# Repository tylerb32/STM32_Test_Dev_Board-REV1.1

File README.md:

# STM32_Test_Dev_Board-REV1.1
*Currently a work in progress<br/>
The purpose of this project is to gain experience with embedded system design, electronics and PCB design, and firmware/real-time software development in FreeRTOS.<br/>
Status: PCBs assembled (Investigating accelerometer hardware implementation).

Changes from REV 1:
- Changed component selection for MCU, crystal oscillator, and accelerometer due to availability and cost constraints
- Added switches for user input
- Improved positioning of LCD headers and ensured the screen won't block any other headers or connectors when plugged in
- Changed micro USB footprint
- Routed CBUS pins from UART-USB bridge and interrupt pins from the accelerometer to the MCU instead of external headers
- Routed remaining pins including LPUART to external headers

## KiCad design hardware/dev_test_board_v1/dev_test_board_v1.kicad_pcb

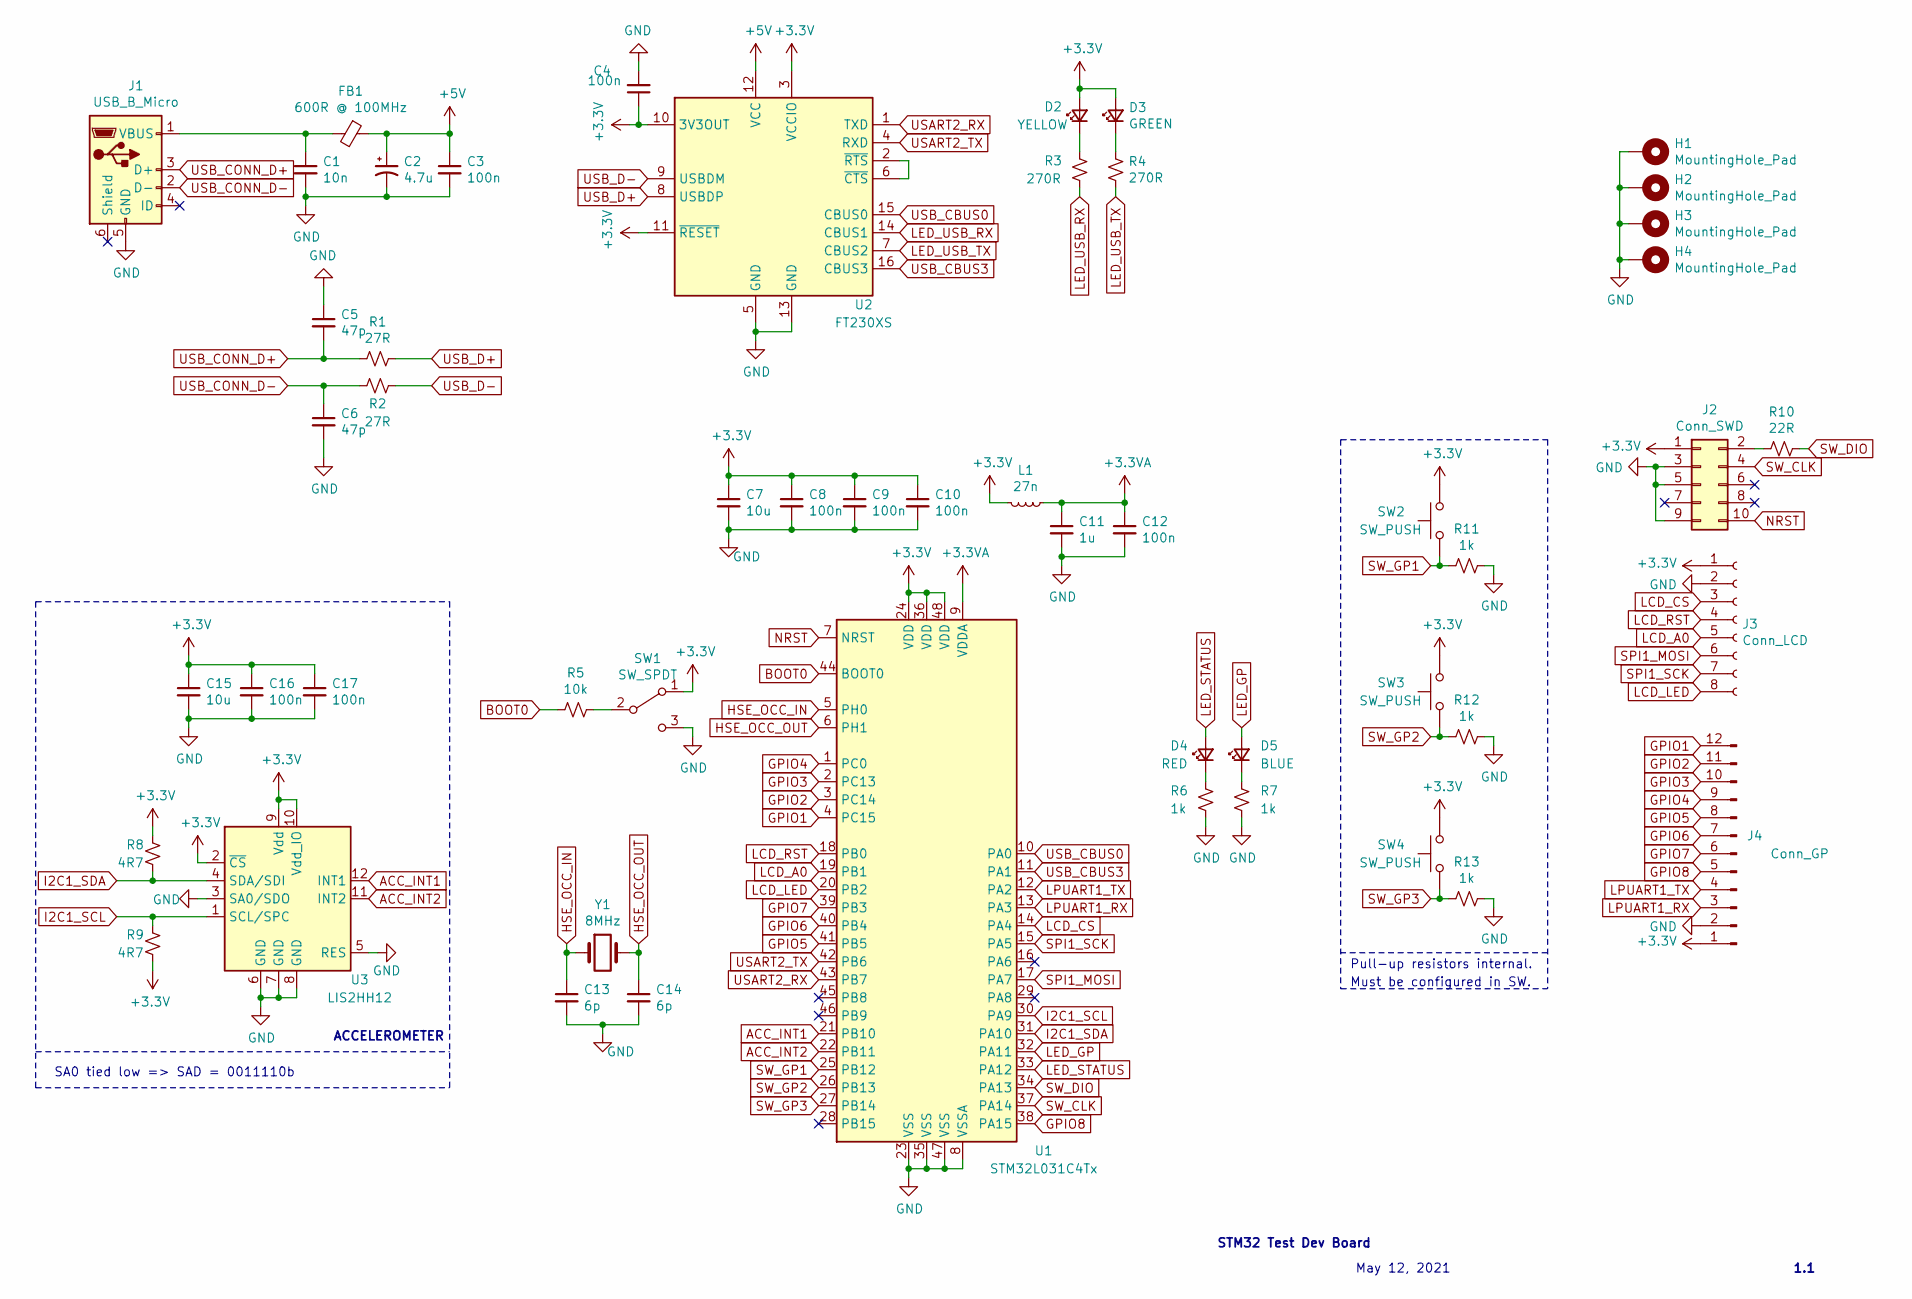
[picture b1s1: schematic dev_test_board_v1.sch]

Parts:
C1: 10n; C_0603_1608Metric
C2: 4.7u; CP_Elec_4x5.4
C3, C4, C8, C9, C10, C12, C16, C17: 100n; C_0402_1005Metric
C5, C6: 47p; C_0603_1608Metric
C7, C15: 10u; C_0402_1005Metric
C11: 1u; C_0402_1005Metric
C13, C14: 6p; C_0402_1005Metric
D2: YELLOW; LED_0603_1608Metric
D3: GREEN; LED_0603_1608Metric
D4: RED; LED_0603_1608Metric
D5: BLUE; LED_0603_1608Metric
FB1: 600R @ 100MHz; L_0805_2012Metric
H1, H2, H3, H4: MountingHole_Pad; MountingHole_2.7mm_M2.5_Pad_Via
J1: USB_B_Micro; UBS_Micro-B_Citzends_Aliexpress
J2: Conn_SWD; PinHeader_2x05_P1.27mm_Vertical
J3: Conn_LCD; PinSocket_1x08_P2.54mm_Vertical
J4: Conn_GP; PinHeader_1x12_P2.54mm_Vertical
L1: 27n; L_0603_1608Metric
R1, R2: 27R; R_0402_1005Metric
R3, R4: 270R; R_0603_1608Metric
R5: 10k; R_0402_1005Metric
R6, R7: 1k; R_0603_1608Metric
R8, R9: 4R7; R_0402_1005Metric
R10: 22R; R_0402_1005Metric
R11, R12, R13: 1k; R_0402_1005Metric
SW1: SW_SPDT; SW_Unknown_SPDT_Straight
SW2, SW3, SW4: SW_PUSH; SW_Push_1P1T_NO_6x6mm_H9.5mm
U1: STM32L031C4Tx; LQFP-48_7x7mm_P0.5mm
U2: FT230XS; SSOP-16_3.9x4.9mm_P0.635mm
U3: LIS2HH12; LGA-12_2x2mm_P0.5mm
Y1: 8MHz; Crystal_NX8045GB

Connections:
+3.3VA: C11.1, C12.1, L1.1, U1.9 (VDDA)
+3V3: C4.1, C7.1, C8.1, C9.1, C10.1, C15.1, C16.1, C17.1, D2.2 (A), D3.2 (A), J2.1, J3.1, J4.1, L1.2, R8.2, R9.1, SW1.1 (A), SW2.2, SW3.2, SW4.2, U1.24 (VDD), U1.36 (VDD), U1.48 (VDD), U2.3 (VCCIO), U2.10 (3V3OUT), U2.11 (~RESET), U3.2 (~CS), U3.9 (Vdd), U3.10 (Vdd_IO)
+5V: C2.1, C3.1, FB1.1, U2.12 (VCC)
ACC_INT1: U1.21 (PB10), U3.12 (INT1)
ACC_INT2: U1.22 (PB11), U3.11 (INT2)
BOOT0: R5.2, U1.44 (BOOT0)
GND: C1.2, C2.2, C3.2, C4.2, C5.1, C6.2, C7.2, C8.2, C9.2, C10.2, C11.2, C12.2, C13.2, C14.2, C15.2, C16.2, C17.2, H1.1, H2.1, H3.1, H4.1, J1.5 (GND), J2.3, J2.5, J2.9, J3.2, J4.2, R6.2, R7.2, R11.1, R12.1, R13.1, SW1.3 (C), U1.8 (VSSA), U1.23 (VSS), U1.35 (VSS), U1.47 (VSS), U2.5 (GND), U2.13 (GND), U3.3 (SA0/SDO), U3.5 (RES), U3.6 (GND), U3.7 (GND), U3.8 (GND)
GPIO1: J4.12, U1.4 (PC15)
GPIO2: J4.11, U1.3 (PC14)
GPIO3: J4.10, U1.2 (PC13)
GPIO4: J4.9, U1.1 (PC0)
GPIO5: J4.8, U1.41 (PB5)
GPIO6: J4.7, U1.40 (PB4)
GPIO7: J4.6, U1.39 (PB3)
GPIO8: J4.5, U1.38 (PA15)
HSE_OCC_IN: C13.1, U1.5 (PH0), Y1.1
HSE_OCC_OUT: C14.1, U1.6 (PH1), Y1.2
I2C1_SCL: R9.2, U1.30 (PA9), U3.1 (SCL/SPC)
I2C1_SDA: R8.1, U1.31 (PA10), U3.4 (SDA/SDI)
LCD_A0: J3.5, U1.19 (PB1)
LCD_CS: J3.3, U1.14 (PA4)
LCD_LED: J3.8, U1.20 (PB2)
LCD_RST: J3.4, U1.18 (PB0)
LED_GP: D5.2 (A), U1.32 (PA11)
LED_STATUS: D4.2 (A), U1.33 (PA12)
LED_USB_RX: R3.2, U2.14 (CBUS1)
LED_USB_TX: R4.2, U2.7 (CBUS2)
LPUART1_RX: J4.3, U1.13 (PA3)
LPUART1_TX: J4.4, U1.12 (PA2)
NRST: J2.10, U1.7 (NRST)
unnamed: C1.1, FB1.2, J1.1 (VBUS)
unnamed: D2.1 (K), R3.1
unnamed: D3.1 (K), R4.1
unnamed: D4.1 (K), R6.1
unnamed: D5.1 (K), R7.1
unnamed: J2.2, R10.2
unnamed: R5.1, SW1.2 (B)
unnamed: U2.2 (~RTS), U2.6 (~CTS)
SPI1_MOSI: J3.6, U1.17 (PA7)
SPI1_SCK: J3.7, U1.15 (PA5)
SW_CLK: J2.4, U1.37 (PA14)
SW_DIO: R10.1, U1.34 (PA13)
SW_GP1: R11.2, SW2.1, U1.25 (PB12)
SW_GP2: R12.2, SW3.1, U1.26 (PB13)
SW_GP3: R13.2, SW4.1, U1.27 (PB14)
USART2_RX: U1.43 (PB7), U2.1 (TXD)
USART2_TX: U1.42 (PB6), U2.4 (RXD)
USB_CBUS0: U1.10 (PA0), U2.15 (CBUS0)
USB_CBUS3: U1.11 (PA1), U2.16 (CBUS3)
USB_CONN_D+: C5.2, J1.3 (D+), R1.2
USB_CONN_D-: C6.1, J1.2 (D-), R2.2
USB_D+: R1.1, U2.8 (USBDP)
USB_D-: R2.1, U2.9 (USBDM)

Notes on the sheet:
May 12, 2021
STM32 Test Dev Board
1.1
SA0 tied low => SAD = 0011110b
ACCELEROMETER
Pull-up resistors internal.
Must be configured in SW.

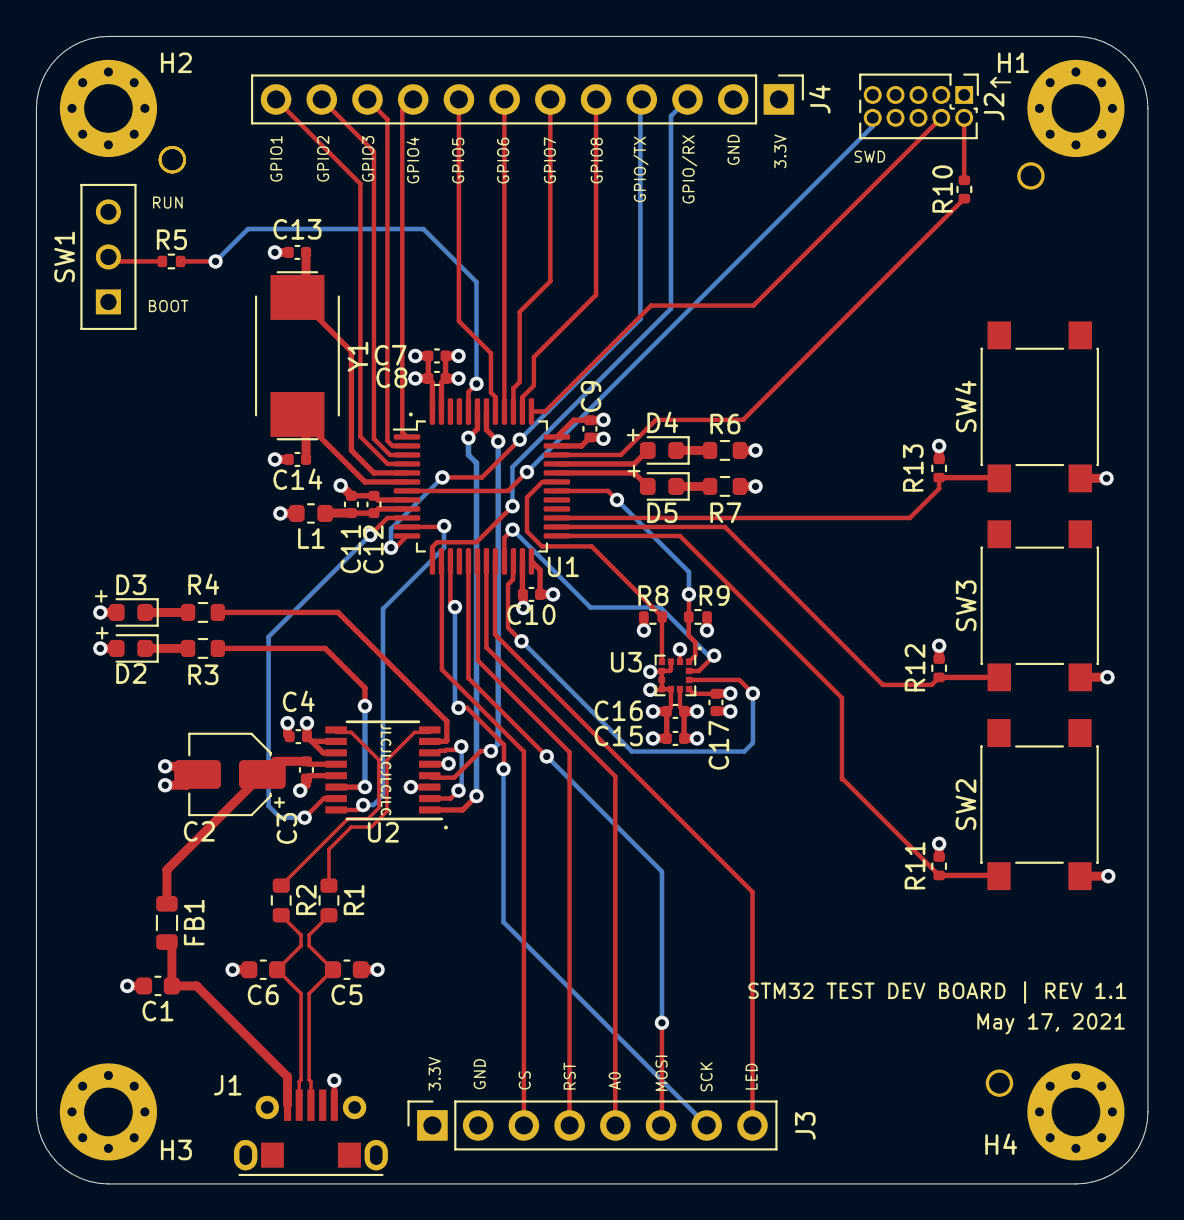
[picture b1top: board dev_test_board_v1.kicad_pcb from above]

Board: 4 copper layers, 61.8 x 63.8 mm, 52 parts (0 on the bottom side), 53 nets.

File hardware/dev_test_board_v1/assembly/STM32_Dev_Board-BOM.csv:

Comment,Designator,Footprint,LCSC
10n,C1,Capacitor_SMD:C_0603_1608Metric,C57112
1u,C11,Capacitor_SMD:C_0402_1005Metric,C52923
6p,"C13,C14",Capacitor_SMD:C_0402_1005Metric,C30274
10u,"C7,C15",Capacitor_SMD:C_0402_1005Metric,C15525
4.7u,C2,Capacitor_SMD:CP_Elec_4x5.4,
100n,"C3,C4,C8,C9,C10,C12,C16,C17",Capacitor_SMD:C_0402_1005Metric,C1525
47p,"C5,C6",Capacitor_SMD:C_0603_1608Metric,C1671
YELLOW,D2,LED_SMD:LED_0603_1608Metric,C72038
GREEN,D3,LED_SMD:LED_0603_1608Metric,C72043
RED,D4,LED_SMD:LED_0603_1608Metric,C2286
BLUE,D5,LED_SMD:LED_0603_1608Metric,C72041
600R @ 100MHz,FB1,Inductor_SMD:L_0805_2012Metric,C1017
MountingHole_Pad,"H1,H2,H3,H4",MountingHole:MountingHole_2.7mm_M2.5_Pad_Via,
USB_B_Micro,J1,tyjba_footprints:UBS_Micro-B_Citzends_Aliexpress,
Conn_SWD,J2,Connector_PinHeader_1.27mm:PinHeader_2x05_P1.27mm_Vertical,
Conn_LCD,J3,Connector_PinSocket_2.54mm:PinSocket_1x08_P2.54mm_Vertical,
Conn_GP,J4,Connector_PinHeader_2.54mm:PinHeader_1x12_P2.54mm_Vertical,
27n,L1,Inductor_SMD:L_0603_1608Metric,C12100
22R,R10,Resistor_SMD:R_0402_1005Metric,C25092
1k,"R11,R12,R13",Resistor_SMD:R_0402_1005Metric,C11702
27R,"R1,R2",Resistor_SMD:R_0603_1608Metric,C25190
270R,"R3,R4",Resistor_SMD:R_0603_1608Metric,C22966
10k,R5,Resistor_SMD:R_0402_1005Metric,C25744
1k,"R6,R7",Resistor_SMD:R_0603_1608Metric,C21190
4R7,"R8,R9",Resistor_SMD:R_0402_1005Metric,C25900
SW_SPDT,SW1,tyjba_footprints:SW_Unknown_SPDT_Straight,
SW_PUSH,"SW2,SW3,SW4",Button_Switch_SMD:SW_Push_1P1T_NO_6x6mm_H9.5mm,
STM32L031C4Tx,U1,Package_QFP:LQFP-48_7x7mm_P0.5mm,
FT230XS,U2,Package_SO:SSOP-16_3.9x4.9mm_P0.635mm,
LIS2HH12,U3,Package_LGA:LGA-12_2x2mm_P0.5mm,
8MHz,Y1,tyjba_footprints:Crystal_NX8045GB,

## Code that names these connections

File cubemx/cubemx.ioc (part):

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Mcu.Name=STM32L031C(4-6)Tx
Mcu.Package=LQFP48
Mcu.UserName=STM32L031C4Tx
PA0.Signal=GPIO_Output
PA1.Signal=GPIO_Output
PA10.Mode=I2C
PA10.Signal=I2C1_SDA
PA11.Signal=GPIO_Output
PA12.Signal=GPIO_Output
PA13.Mode=Serial_Wire
PA13.Signal=SYS_SWDIO
PA14.Mode=Serial_Wire
PA14.Signal=SYS_SWCLK
PA15.Signal=GPIO_Input
PA2.Mode=Asynchronous
PA2.Signal=LPUART1_TX
PA3.Mode=Asynchronous
PA3.Signal=LPUART1_RX
PA4.Signal=GPIO_Output
PA5.Mode=Simplex_Bidirectional_Master
PA5.Signal=SPI1_SCK
PA7.Mode=Simplex_Bidirectional_Master
PA7.Signal=SPI1_MOSI
PA9.Mode=I2C
PA9.Signal=I2C1_SCL
PB0.Signal=GPIO_Output
PB1.Signal=GPIO_Output
PB10.Signal=GPIO_Output
PB11.Signal=GPIO_Output
PB12.Signal=GPIO_Input
PB13.Signal=GPIO_Input
PB14.Signal=GPIO_Input
PB2.Signal=GPIO_Output
PB3.Signal=GPIO_Input
PB4.Signal=GPIO_Input
PB5.Signal=GPIO_Input
PB6.Mode=Asynchronous
PB6.Signal=USART2_TX
PB7.Mode=Asynchronous
PB7.Signal=USART2_RX
PC0.Signal=GPIO_Input
PC13-ANTI_TAMP.Signal=GPIO_Input
PC14-OSC32_IN.Signal=GPIO_Input
PC15-OSC32_OUT.Signal=GPIO_Input
PH0-OSC_IN.Mode=HSE-External-Oscillator
PH0-OSC_IN.Signal=RCC_OSC_IN
PH1-OSC_OUT.Mode=HSE-External-Oscillator
PH1-OSC_OUT.Signal=RCC_OSC_OUT
RCC.HSE_VALUE=8000000
RCC.SYSCLKFreq_VALUE=2097000
board=custom

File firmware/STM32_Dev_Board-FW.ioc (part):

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PB13.GPIOParameters=GPIO_Label
PH0-OSC_IN.Signal=RCC_OSC_IN
PA7.Mode=Simplex_Bidirectional_Master
PA10.Mode=I2C
Mcu.UserName=STM32L031C4Tx
PB14.GPIO_Label=SW_GP3
PA12.GPIOParameters=GPIO_Label
PA11.GPIOParameters=GPIO_Label
PA11.GPIO_Label=LED_GP
PB0.GPIO_Label=LCD_RST
PB13.GPIO_Label=SW_GP2
PB13.Signal=GPIO_Input
PA12.GPIO_Label=LED_STATUS
RCC.SYSCLKSource=RCC_SYSCLKSOURCE_HSE
PA13.Signal=SYS_SWDIO
PA9.Mode=I2C
PA12.Signal=GPIO_Output
PB10.GPIO_Label=ACC_INT1_EXT
PA9.Signal=I2C1_SCL
PB2.GPIOParameters=GPIO_Label
PB6.Signal=USART2_TX
PB6.Mode=Asynchronous
PA1.Signal=GPIO_Input
PH0-OSC_IN.Mode=HSE-External-Oscillator
PB10.Signal=GPXTI10
PB14.Signal=GPIO_Input
PA5.Signal=SPI1_SCK
RCC.HSE_VALUE=8000000
PB2.Signal=GPIO_Output
board=custom
PB12.GPIO_Label=SW_GP1
PB0.GPIOParameters=GPIO_Label
PA1.GPIOParameters=GPIO_Label
PA14.Mode=Serial_Wire
PB1.GPIO_Label=LCD_A0
PA1.GPIO_Label=USB_CBUS3
PH1-OSC_OUT.Signal=RCC_OSC_OUT
PB7.Signal=USART2_RX
PA4.GPIOParameters=GPIO_Label
PA13.Mode=Serial_Wire
PB10.GPIO_ModeDefaultEXTI=GPIO_MODE_IT_RISING
Mcu.Name=STM32L031C(4-6)Tx
PH1-OSC_OUT.Mode=HSE-External-Oscillator
PA4.Signal=GPIO_Output
RCC.SYSCLKFreq_VALUE=8000000
Mcu.Package=LQFP48
PB1.Signal=GPIO_Output
PA11.Signal=GPIO_Output
PB7.Mode=Asynchronous
PA10.Signal=I2C1_SDA
PA14.Signal=SYS_SWCLK
PB2.GPIO_Label=LCD_LED
PB14.GPIOParameters=GPIO_Label
PB10.GPIOParameters=GPIO_Label,GPIO_ModeDefaultEXTI
PB0.Signal=GPIO_Output
PA4.GPIO_Label=LCD_CS
PB12.GPIOParameters=GPIO_Label
PB12.Signal=GPIO_Input
PB1.GPIOParameters=GPIO_Label
PA5.Mode=Simplex_Bidirectional_Master
PA7.Signal=SPI1_MOSI

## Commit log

2021-05-12 Fixed gitignore file.
2021-05-12 All needed pins assigned.
2021-05-13 Components labelled, HSE oscillator added.
2021-05-15 Started PCB layout.
2021-05-15 Draft layout complete.
2021-05-16 All signals routed.
2021-05-17 Removed HW debouncing for SW2-4, finished routing.
2021-05-18 Fixed via placement errors. Added silkscreen for annotations.
2021-05-24 Routing cleaned up a bit and PCBs ordered.
2021-05-24 Fixed 3D models for switches.
2021-06-06 Started FW dev project.
2022-01-19 I2C driver push - suspected hardware failure
